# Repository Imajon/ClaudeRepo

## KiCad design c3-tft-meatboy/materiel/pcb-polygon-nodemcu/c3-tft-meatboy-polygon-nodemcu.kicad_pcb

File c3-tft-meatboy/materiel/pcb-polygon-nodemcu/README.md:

# c3-tft-meatboy — PCB "polygon.svg" + ESP32 DevKit V1 30 broches (ELEGOO) + HP + prototypage

Variante du PCB `c3-tft-meatboy` (contour exact de `../polygon.svg`,
110 x 75.5mm, ecran + boutons identiques a `../pcb-polygon/`), avec
trois changements :

1. **Controleur ESP32 "DevKit V1" 30 broches**, verifie correspondre
   au format de la carte **ELEGOO ESP-WROOM-32** de l'utilisateur
   (voir ci-dessous — un premier essai avec un NodeMCU-32S 38 broches
   etait incorrect, corrige suite a verification).
2. **2 pastilles pour mini haut-parleur** (face avant).
3. **6 pastilles de prototypage** (face arriere, broches libres du
   controleur).

## Controleur : ESP32 DevKit V1, 30 broches (dos)
2 rangees de **15 broches**, pas 2.54mm, **entraxe 22.86mm (0.9",
"900 mil")**, empreinte ~51.8 x 28.2mm.

**Pastilles traversantes (PTH/percees), pas CMS** — les cartes ELEGOO
ont generalement leurs broches males deja soudees en usine, il faut
donc des trous pour les enficher (et souder cote oppose), pas de
pastilles de surface. La colonne de broches a ete repositionnee (a
DROITE du bouton DROITE plutot qu'au milieu du groupe de boutons) car
des pastilles traversantes ont du cuivre sur F.Cu ET B.Cu meme sur
une broche non utilisee — l'ancien emplacement (au milieu de la
largeur du bouton DROITE) faisait percuter le pont interne du bouton
par une broche du controleur.

**Correction importante** : la 1ere version de ce fichier utilisait le
format "NodeMCU-32S/DevKitC" (38 broches, entraxe 25.4mm/1"), qui est
un AUTRE format d'empreinte ESP32 tres repandu mais different. Apres
verification, les cartes ELEGOO ESP-WROOM-32 (et la plupart des clones
"ESP32 DevKit V1") utilisent le format **30 broches / 15 par rangee /
entraxe 0.9"**, repris ici. Sources verifiees en ligne : dimensions
carte ~51.8 x 28.2mm, 15 broches par rangee, pas 2.54mm standard
("900 mil" = 22.86mm entre rangees). Si ta carte differe (certains
clones ELEGOO existent aussi en 36 ou 38 broches), verifie au pied a
coulisse avant de commander.

**Numerotation generique (broche 1 a 15 par rangee), pas les noms de
silkscreen (GPIOxx) imprimes sur la carte ELEGOO** — il faudra
identifier quelle broche physique (position) correspond a quel GPIO
sur TA carte reelle (le manuel ELEGOO ou une photo annotee de la carte
donnent cette correspondance) avant de souder, et adapter le firmware
en consequence.

- **J1** (rangee gauche) : broche1=DROITE, broche2=GND, broche3=GAUCHE,
  broche4=+3V3, broche5=HP (signal haut-parleur), broches 6-15 libres.
- **J2** (rangee droite) : broches 1-6=PROTO1-6 (prototypage), broche7=GND,
  broche8=+3V3, broche9=SCLK, broche10=MOSI, broche11=RST, broche12=DC,
  broche13=CS, broche14=SAUT, broche15 libre.

## Mini haut-parleur (face avant, 2 pastilles traversantes)
2 pastilles Ø2.5mm (percage Ø1.2mm) pres du centre de la carte, pour
souder directement les 2 fils d'un mini haut-parleur : une va a une
broche GPIO du controleur (signal, via J1 broche5), l'autre a la
masse. **Pas de circuit d'attaque (ampli/transistor) sur ce PCB** —
pour un son audible il faut presque toujours un petit ampli (ex.
PAM8302) ou au minimum un transistor de puissance entre le GPIO et le
haut-parleur ; piloter le haut-parleur en PWM direct depuis le GPIO ne
fonctionne qu'avec de tres petits buzzers piezo basse consommation. A
verifier selon le haut-parleur choisi.

## Pastilles de prototypage (face arriere)
6 broches du controleur (J2, broches 1-6) sont routees vers rien
d'autre que leur propre pastille CMS — elles restent disponibles,
cote dos, pour souder des fils vers d'autres composants au gre des
besoins (capteurs, LED, etc.). Choisies parmi les broches non
utilisees par l'ecran/les boutons/le HP ; **le mapping GPIO reel
depend du module** (meme reserve que ci-dessus).

## Fichiers
- `c3-tft-meatboy-polygon-nodemcu.kicad_pcb` — projet KiCad 10.
  **DRC : 0 erreur, 0 element non connecte.**
- `gerbers/` + `c3-tft-meatboy-polygon-nodemcu-gerbers.zip` — prets a
  envoyer a un fabricant (JLCPCB, PCBWay...), 2 couches, FR4, 1.6mm.

## Notes de routage
- Meme principe "peigne imbrique" que les autres variantes (ordre
  broche/cible croissants ensemble) pour GND/+3V3/SCLK/MOSI/RST/DC/CS.
- **Piege recurrent avec des pastilles traversantes** : contrairement
  aux pastilles CMS (une seule couche), une pastille PTH a du cuivre
  sur F.Cu ET B.Cu — meme non utilisee. Plusieurs trajets ont du etre
  redessines pour ne jamais "reculer" sur la colonne du controleur ni
  friser une pastille de bouton voisine (SAUT notamment, coince entre
  sa propre pastille GND et une broche du controleur). Regle
  generale : sortir immediatement de la colonne (segment court, une
  seule valeur de y) avant toute diagonale ou tout detour.
- Le debut de la colonne de broches est assez proche des pastilles
  ecran en Y (memes coordonnees a ~0.2mm pres par endroits, decalage
  constant du au meme pas 2.54mm des deux cotes) : resolu en placant
  la carte plus bas (Y de depart 32mm) et en choisissant les broches
  7-13 (nettement au-dessus, >=11.5mm, de toutes les cibles J3) pour
  les 7 signaux ecran ; les broches 1-6, plus proches de cette zone,
  servent au prototypage ou elles ne portent aucune piste donc aucun
  risque.
- Le jumper +3V3 (J1.4 -> J2.8) devait eviter les 2 pastilles HP puis
  l'approche laterale de J2 (pas tout droit dans la colonne, qui
  aurait percute la pastille voisine) — 2 detours ajoutes.
- **Pas un seul via sur toute la carte** : les pastilles du
  controleur et de l'ecran sont maintenant toutes traversantes (PTH),
  donc une piste peut partir directement en F.Cu ou B.Cu depuis
  n'importe laquelle sans changement de couche. Seule exception :
  DROITE reste en B.Cu jusqu'a un via juste avant sa pastille de
  bouton CMS (qui, elle, reste F.Cu uniquement).

## AVANT de commander
1. **Module ESP32 DevKit V1 / ELEGOO** : compte les broches sur ta
   carte reelle (doit faire 15 par rangee, 30 au total) et verifie
   l'entraxe (~22.86mm) au pied a coulisse.
2. **Mapping GPIO reel** : voir avertissement ci-dessus (brochage
   generique, pas les noms silkscreen).
3. **Haut-parleur** : verifie s'il te faut un ampli entre le GPIO et
   les pastilles HP (voir section dediee).
4. Boutons 6x6mm/12x12mm et ecran : memes fiches techniques verifiees
   que les versions precedentes (voir `../pcb/README.md`).

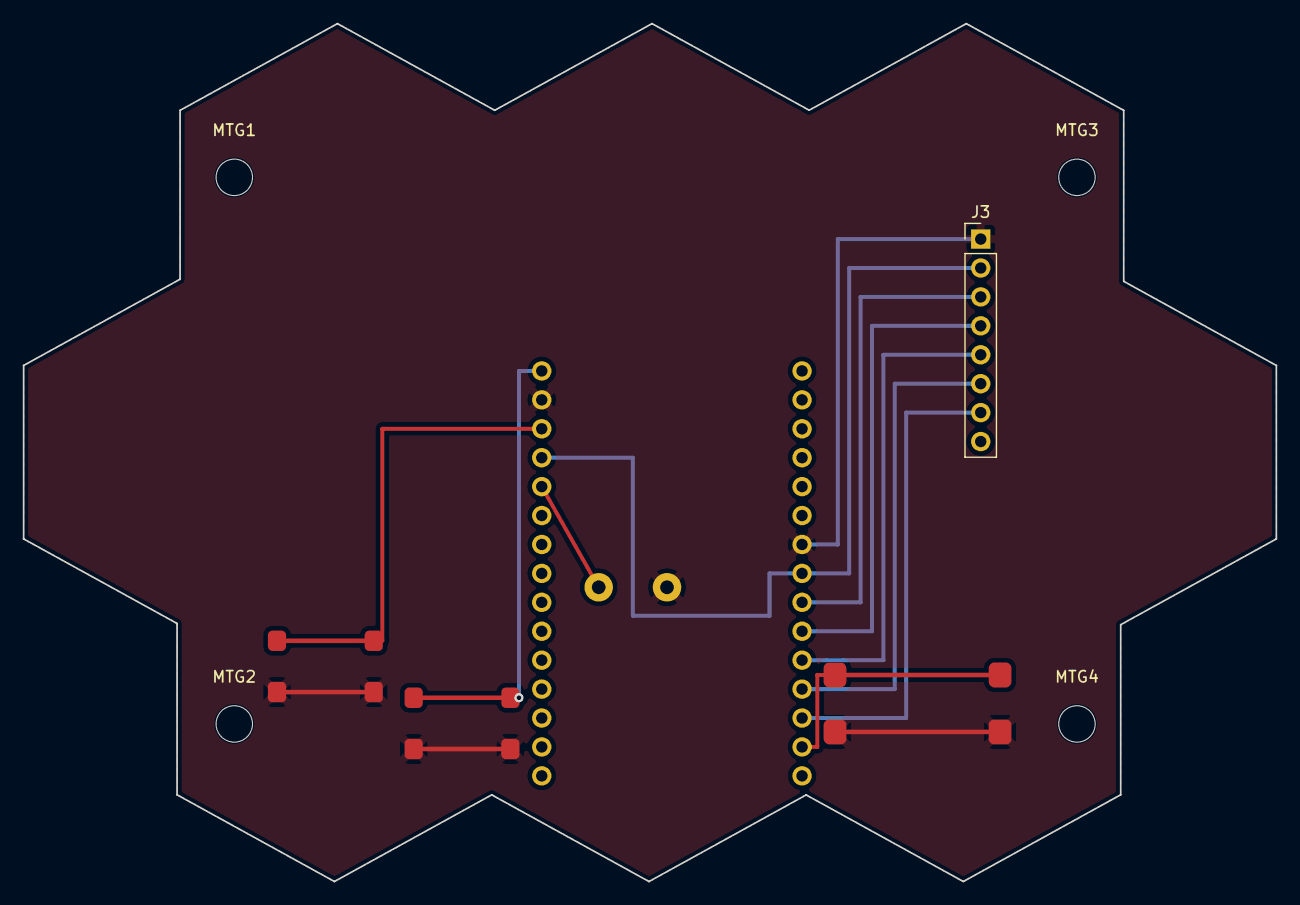
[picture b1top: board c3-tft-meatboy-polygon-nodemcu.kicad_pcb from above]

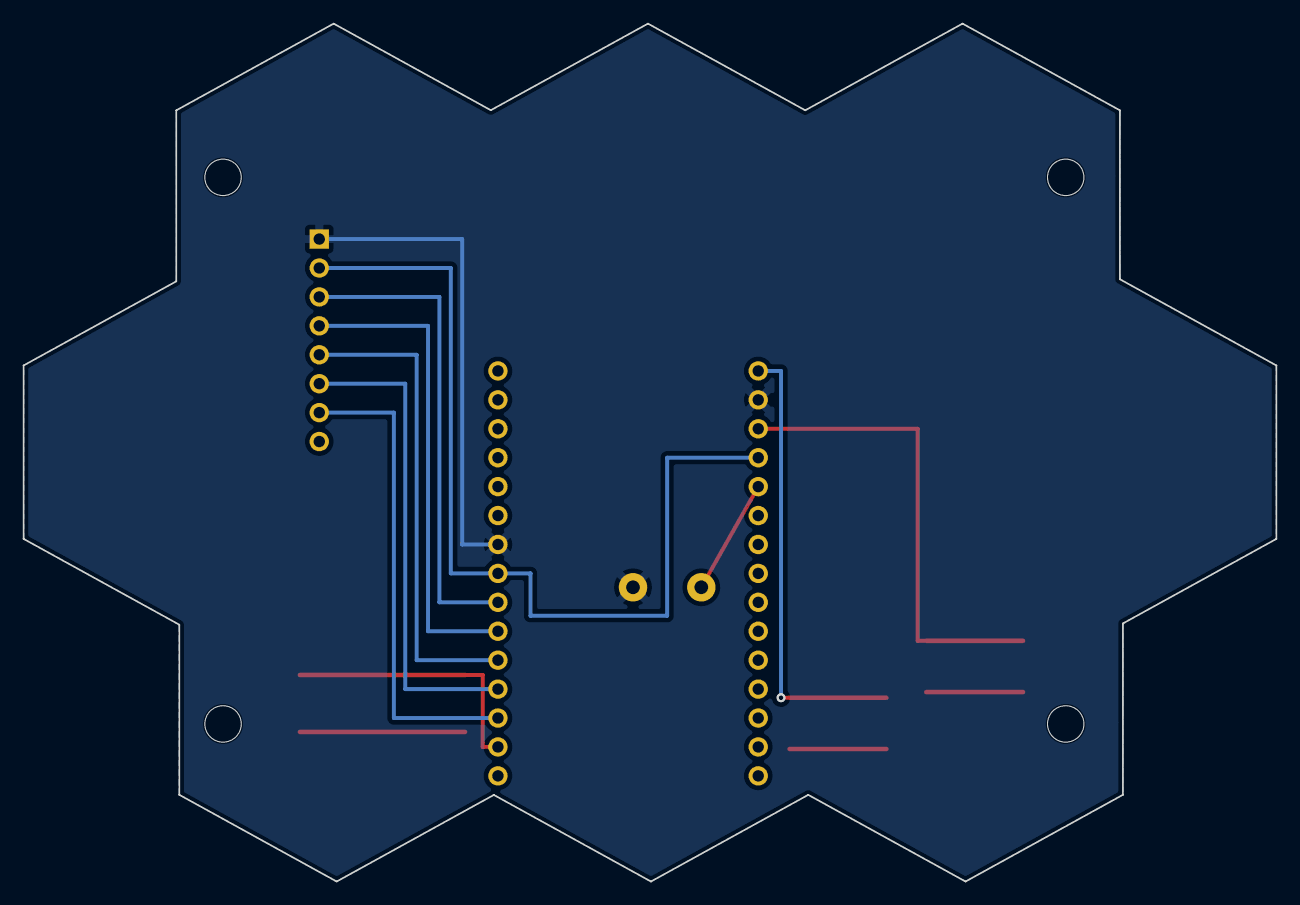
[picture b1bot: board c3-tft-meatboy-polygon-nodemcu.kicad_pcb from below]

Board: 2 copper layers, 110.0 x 75.3 mm, 11 parts (2 on the bottom side), 11 nets.

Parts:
J1, J2: (no value)
J3: PinHeader_1x08_P2.54mm_Vertical
MTG1, MTG2, MTG3, MTG4: MountingHole_3.2mm_M3
SPK: (no value)
SW1, SW2, SW3: (no value)

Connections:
+3V3: J1.4, J2.8, J3.2
GND: J1.2, J2.7, J3.1, SPK.2, SW1.2, SW2.2, SW3.2
GPIO4_SAUT: J2.14, SW3.1
GPIO18_SCLK: J2.9, J3.3
GPIO23_MOSI: J2.10, J3.4
GPIO25_RST: J2.11, J3.5
GPIO26_DC: J2.12, J3.6
GPIO27_CS: J2.13, J3.7
GPIO32_DROITE: J1.1, SW2.1
GPIO33_GAUCHE: J1.3, SW1.1
GPIO_SPKR: J1.5, SPK.1

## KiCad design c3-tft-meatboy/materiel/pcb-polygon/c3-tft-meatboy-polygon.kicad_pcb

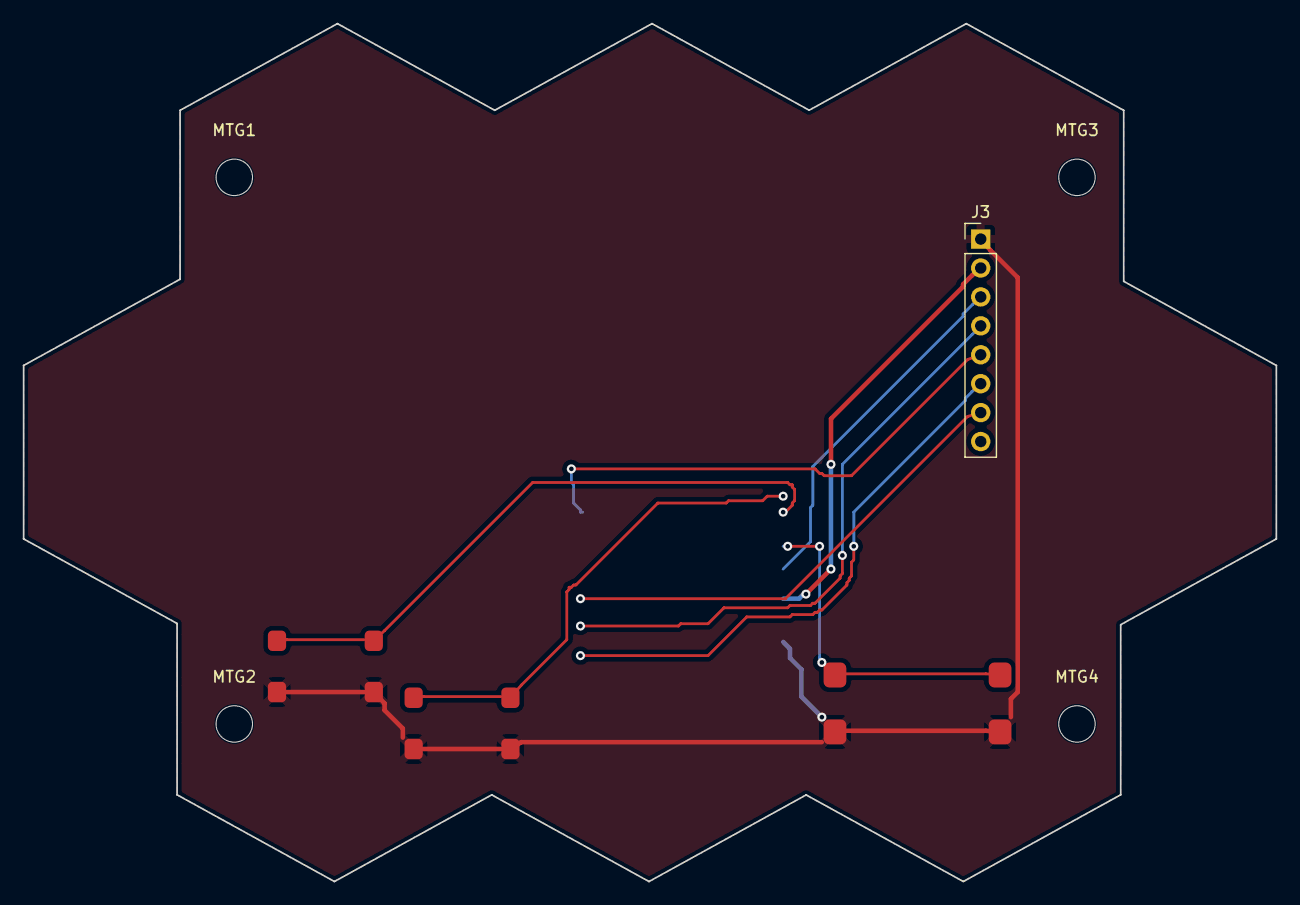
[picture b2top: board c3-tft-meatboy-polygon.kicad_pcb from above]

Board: 2 copper layers, 110.0 x 75.3 mm, 9 parts (1 on the bottom side), 10 nets.

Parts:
J3: PinHeader_1x08_P2.54mm_Vertical
MTG1, MTG2, MTG3, MTG4: MountingHole_3.2mm_M3
SW1, SW2, SW3: (no value)
U1: ESP32-C3_SuperMini_SMD

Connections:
+3V3: J3.2, U1.6
CS: J3.7, U1.14
DC: J3.6, U1.16
DROITE: SW2.1, U1.2
GAUCHE: SW1.1, U1.3
GND: J3.1, SW1.2, SW2.2, SW3.2, U1.7
MOSI: J3.4, U1.15
RST: J3.5, U1.11
SAUT: SW3.1, U1.4
SCLK: J3.3, U1.5
